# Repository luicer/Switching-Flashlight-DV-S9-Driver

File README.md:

# Switching driver for diving flashlight  DV-S9
Design of an adjustable switching regulator driver for DV-S9 diving flashlight, supporting current up to 1 A and input voltage between 3V and 4.2V, along with low standby current. The driver achieves up to 85% efficiency at maximum current. This design is open source hardware.

Post where the design is esplained:
[https://luicer.github.io/led%20flashlight/Flashlight-Driver-Switching-Eng/](https://luicer.github.io/led%20flashlight/Flashlight-Driver-Switching-Eng/)

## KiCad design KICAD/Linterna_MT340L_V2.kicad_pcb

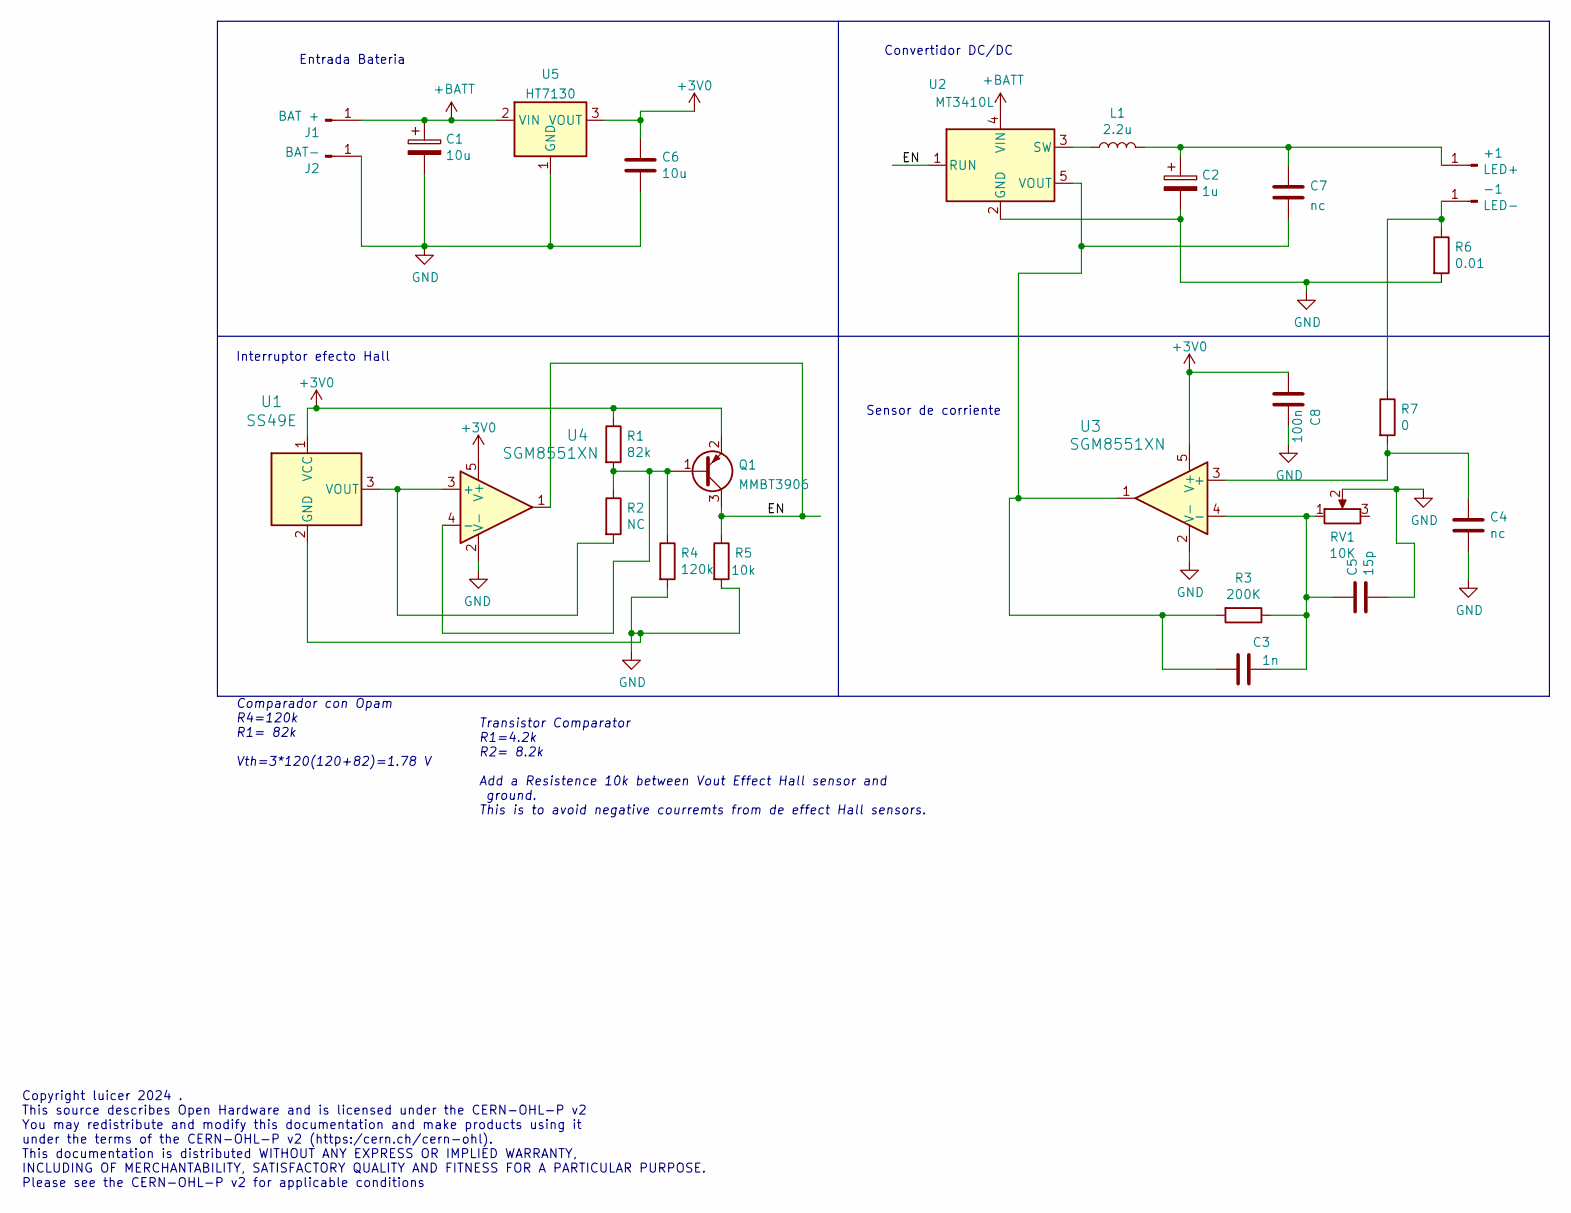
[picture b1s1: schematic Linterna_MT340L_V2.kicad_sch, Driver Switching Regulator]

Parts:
+1: LED+; Solder_Pad3_3
-1: LED-; Solder_Pad3_3
C1: 10u; CP_EIA-3216-18_Kemet-A_Pad1.58x1.35mm_HandSolder
C2: 1u; C_0805_2012Metric_Pad1.15x1.40mm_HandSolder
C3: 1n; C_0805_2012Metric_Pad1.15x1.40mm_HandSolder
C4: nc; C_0805_2012Metric_Pad1.15x1.40mm_HandSolder
C5: 15p; C_0805_2012Metric_Pad1.15x1.40mm_HandSolder
C6: 10u; C_0805_2012Metric_Pad1.18x1.45mm_HandSolder
C7: nc; C_0805_2012Metric_Pad1.18x1.45mm_HandSolder
C8: 100n; C_0805_2012Metric_Pad1.18x1.45mm_HandSolder
J1: BAT +; Lin_Pad+
J2: BAT-; Lin_Pad-
L1: 2.2u; CD43NP-100MC
Q1: MMBT3906; SOT-23
R1: 82k; R_0805_2012Metric_Pad1.15x1.40mm_HandSolder
R2: NC; R_0805_2012Metric_Pad1.15x1.40mm_HandSolder
R3: 200K; R_0805_2012Metric_Pad1.15x1.40mm_HandSolder
R4: 120k; R_0805_2012Metric_Pad1.15x1.40mm_HandSolder
R5: 10k; R_0805_2012Metric_Pad1.15x1.40mm_HandSolder
R6: 0.01; R_2512_6332Metric_Pad1.52x3.35mm_HandSolder
R7: 0; R_0805_2012Metric_Pad1.15x1.40mm_HandSolder
RV1: 10K; TC33X-2-103E
U1: SS49E
U2: MT3410L; TSOT-23-5
U3, U4: SGM8551XN; SOT-23-5
U5: HT7130; SOT-89-3

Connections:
+3V0: C6.1, C8.2, Q1.2 (E), R1.1, U1.1 (VCC), U3.5 (V+), U4.5 (V+), U5.3 (VOUT)
+BATT: C1.1, J1.1, U2.4 (VIN), U5.2 (VIN)
/EN: Q1.3 (C), R5.1, U2.1 (RUN), U4.1
GND: C1.2, C2.2, C4.2, C5.2, C6.2, C8.1, J2.1, R4.2, R5.2, R6.2, RV1.2, U1.2 (GND), U2.2 (GND), U3.2 (V-), U4.2 (V-), U5.1 (GND)
unnamed: +1.1, C2.1, C7.1, L1.2
unnamed: -1.1, R6.1, R7.1
unnamed: C3.1, C5.1, R3.1, RV1.1, U3.4 (-)
unnamed: C3.2, C7.2, R3.2, U2.5 (VOUT), U3.1
unnamed: C4.1, R7.2, U3.3 (+)
unnamed: L1.1, U2.3 (SW)
unnamed: Q1.1 (B), R1.2, R2.1, R4.1, U4.4 (-)
unnamed: R2.2, U1.3 (VOUT), U4.3 (+)

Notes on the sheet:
Transistor Comparator R1=4.2k R2= 8.2k Add a Resistence 10k between Vout Effect Hall sensor and ground. This is to avoid negative courremts from de effect Hall sensors.
Copyright luicer 2024 . This source describes Open Hardware and is licensed under the CERN-OHL-P v2 You may redistribute and modify this documentation and make products using it under the terms of the CERN-OHL-P v2 (https:/cern.ch/cern-ohl). This documentation is distributed WITHOUT ANY EXPRESS OR 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
Convertidor DC/DC
Entrada Bateria
Interruptor efecto Hall
Sensor de corriente
Comparador con Opam R4=120k R1= 82k Vth=3*120(120+82)=1.78 V

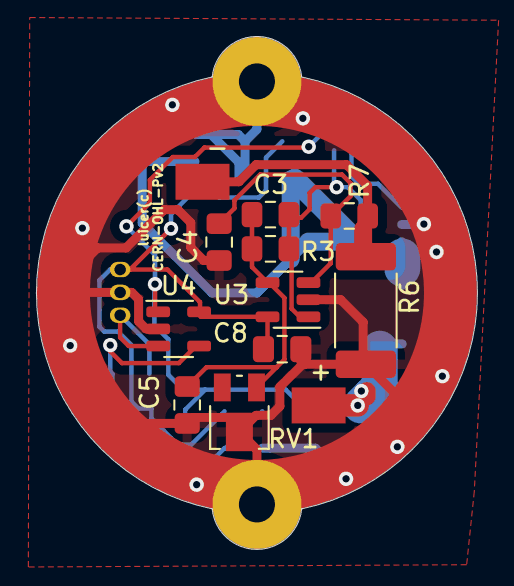
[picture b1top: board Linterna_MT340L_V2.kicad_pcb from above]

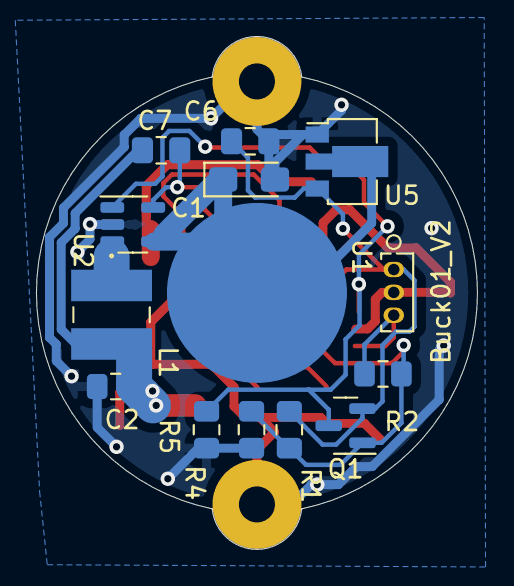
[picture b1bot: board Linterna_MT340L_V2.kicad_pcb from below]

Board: 2 copper layers, 24.5 x 28.5 mm, 27 parts (14 on the bottom side), 12 nets.

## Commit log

2024-03-28 File charge

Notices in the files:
parts and their libraries:
Copyright 2021 Accelerated Designs. All rights reserved.
